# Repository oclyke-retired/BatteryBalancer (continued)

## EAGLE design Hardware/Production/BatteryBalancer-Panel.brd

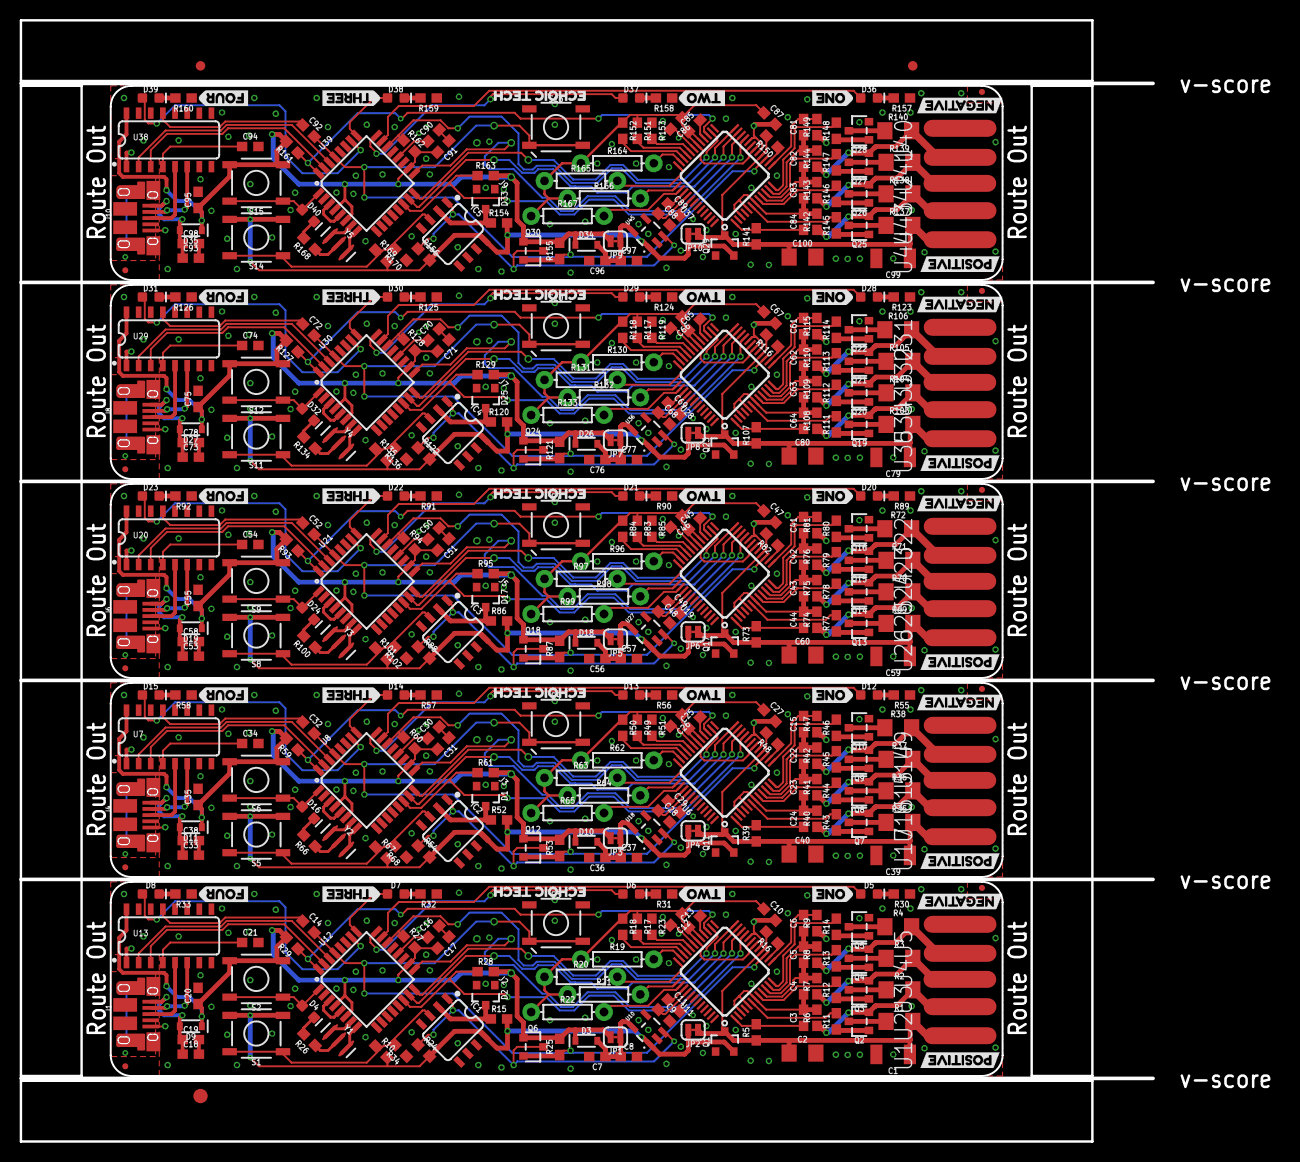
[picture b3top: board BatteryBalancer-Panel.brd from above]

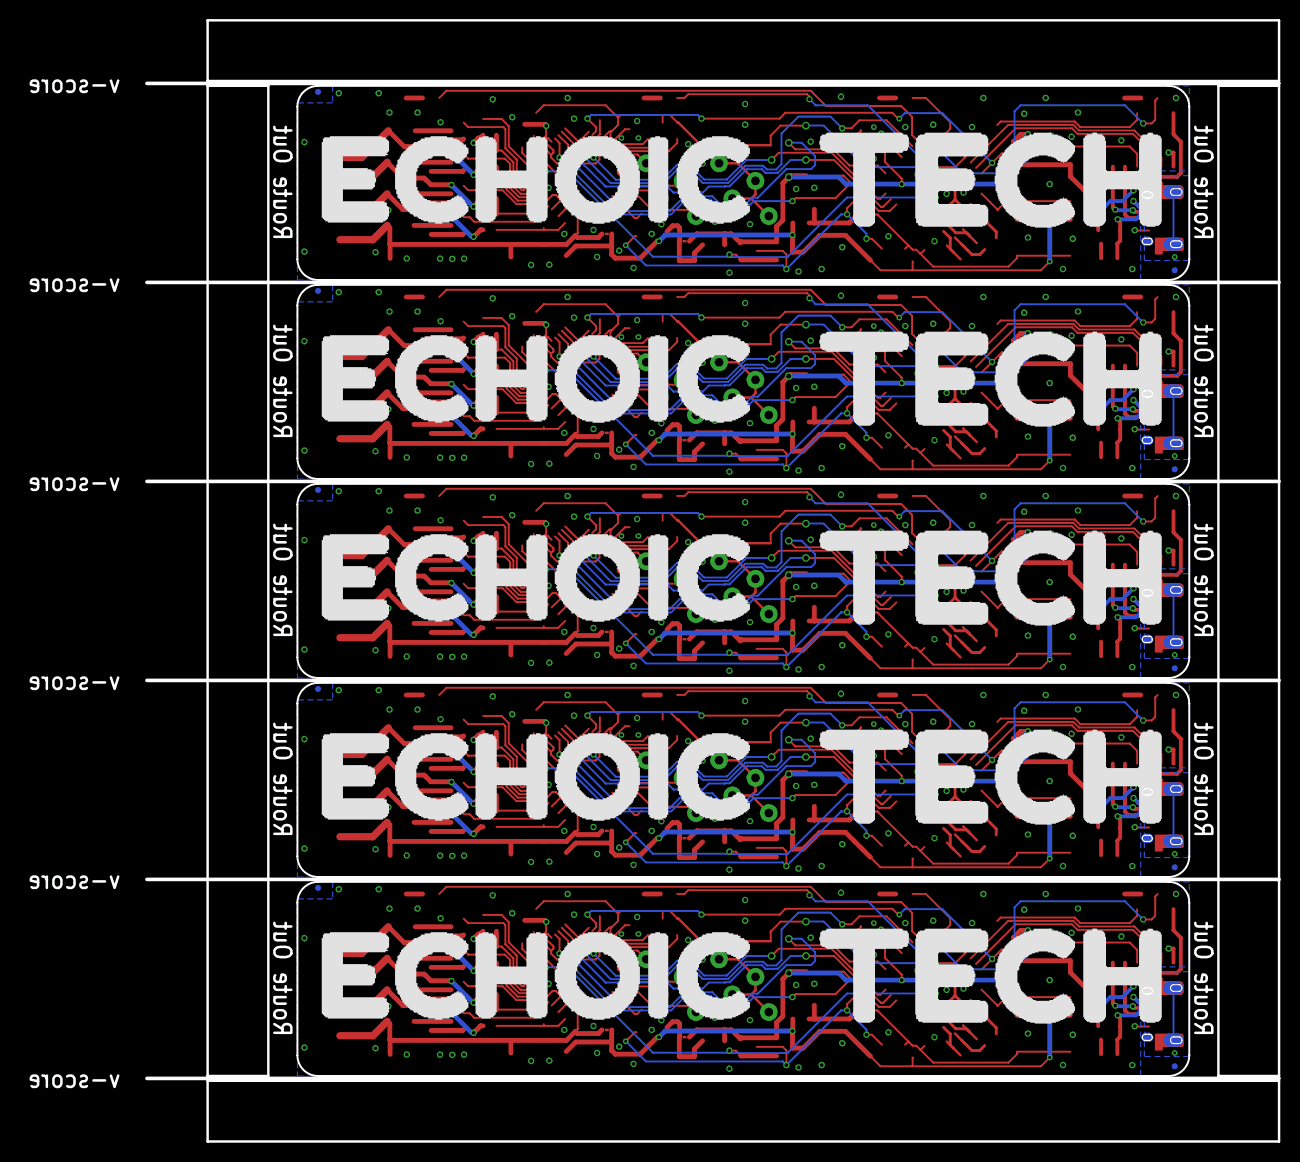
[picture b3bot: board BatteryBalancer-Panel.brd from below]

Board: 2 copper layers, 118.5 x 117.3 mm, 498 parts (20 on the bottom side), 335 nets.

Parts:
C1, C39, C59, C79, C99: 10uF; 1210
C2, C40, C60, C80, C100: 1.0uF; 1206
C3, C4, C5, C6, C8, C10, C12, C14, C15, C16, C17, C18, C20, C22, C23, C24, C26, C27, C30, C31, C32, C33, C35, C37, C41, C42, C43, C44, C46, C47, C50, C51, C52, C53, C55, C57, C61, C62, C63, C64, C66, C67, C70, C71, C72, C73, C75, C77, C81, C82, C83, C84, C86, C87, C90, C91, C92, C93, C95, C97: 0.1uF; 0603
C7, C9, C11, C13, C19, C25, C28, C29, C36, C38, C45, C48, C49, C56, C58, C65, C68, C69, C76, C78, C85, C88, C89, C96, C98: 1.0uF; 0603
C21, C34, C54, C74, C94: 10nF; 0603
D1, D2, D17, D25, D33: TH-12V; SOT23-3
D3, D9, D10, D11, D18, D19, D26, D27, D34, D35: 3A/10V/280mV; SOD-323
D4, D5, D6, D7, D8, D12, D13, D14, D15, D16, D20, D21, D22, D23, D24, D28, D29, D30, D31, D32, D36, D37, D38, D39, D40: BLUE; LED-0603
E$1, E$2: FIDUCIAL-1X2
E$3: FIDUCIAL-1.5X3
FD1, FD2, FD3, FD4, FD5, FD6, FD7, FD8, FD9, FD10, FD11, FD12, FD13, FD14, FD15, FD16, FD17, FD18, FD19, FD20: FIDUCIALUFIDUCIAL; FIDUCIAL-MICRO
IC1, IC2, IC3, IC4, IC5: OP-AMP; SO08
J1, J4, J6, J8, J10: USB-MICROB-PTH-MILL
J2, J3, J5, J7, J9: ISP; 2X3_TEST_POINTS
JP1, JP3, JP5, JP7, JP9: VCC; SMT-JUMPER_2_NC_TRACE_SILK
JP2, JP4, JP6, JP8, JP10: RPP_BYP; SMT-JUMPER_2_NC_TRACE_SILK
Q1, Q2, Q3, Q4, Q5, Q6, Q7, Q8, Q9, Q10, Q11, Q12, Q13, Q14, Q15, Q16, Q17, Q18, Q19, Q20, Q21, Q22, Q23, Q24, Q25, Q26, Q27, Q28, Q29, Q30: SOT23-3
R1, R2, R3, R4, R35, R36, R37, R38, R69, R70, R71, R72, R103, R104, R105, R106, R137, R138, R139, R140: 10; 1206
R5, R6, R7, R8, R9, R11, R12, R13, R14, R16, R17, R18, R23, R24, R25, R26, R27, R28, R29, R39, R40, R41, R42, R43, R44, R45, R46, R47, R48, R49, R50, R51, R53, R54, R59, R60, R61, R66, R73, R74, R75, R76, R77, R78, R79, R80, R81, R82, R83, R84, R85, R87, R88, R93, R94, R95, R100, R107, R108, R109, R110, R111, R112, R113, R114, R115, R116, R117, R118, R119, R121, R122, R127, R128, R129, R134, R141, R142, R143, R144, R145, R146, R147, R148, R149, R150, R151, R152, R153, R155, R156, R161, R162, R163, R168: 10k; 0603
R10, R15, R52, R67, R86, R101, R120, R135, R154, R169: 330k; 0603
R19, R20, R21, R22, R62, R63, R64, R65, R96, R97, R98, R99, R130, R131, R132, R133, R164, R165, R166, R167: DNP; AXIAL-0.3
R30, R31, R32, R33, R55, R56, R57, R58, R89, R90, R91, R92, R123, R124, R125, R126, R157, R158, R159, R160: 1k; 0603
R34, R68, R102, R136, R170: 10M; 0603
S1, S5, S8, S11, S14: Force Charge; TACTILE_SWITCH_SMD_5.2MM
S2, S6, S9, S12, S15: TEST; TACTILE_SWITCH_SMD_5.2MM
S3, S4, S7, S10, S13: Tall Switch; TACTILE_SWITCH_SMD_5.2MM
U1, U2, U3, U4, U5, U9, U14, U15, U16, U17, U22, U23, U24, U25, U26, U31, U32, U33, U34, U35, U40, U41, U42, U43, U44: TAP_POINT; 1X01_SMD_0.1IN
U6, U11, U19, U28, U37: AD7280A; LQFP-48
U7, U13, U20, U29, U38: CH340C; SO016
U8, U12, U21, U30, U39: ATMEGA328P_TQFP; TQFP32-08
U10, U18, U27, U36, U45: MCP1755; SOT23-5
U$1, U$11, U$20, U$29, U$38: POSITIVE1
U$2, U$10, U$19, U$28, U$37: NEGATIVE0
U$3, U$12, U$21, U$30, U$39: ONE3
U$4, U$13, U$22, U$31, U$40: TWO4
U$5, U$14, U$23, U$32, U$41: THREE6
U$6, U$15, U$24, U$33, U$42: FOUR5
U$7, U$16, U$25, U$34, U$43: ECHOIC_TECH7
U$8, U$17, U$26, U$35, U$44: ECHOIC#JPG
U$9, U$18, U$27, U$36, U$45: TECH#JPG
Y1, Y2, Y3, Y4, Y5: 16MHz; RESONATOR-SMD-3.2X1.3

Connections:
5V: C7.1, C8.1, D3.A, JP1.1, U10.5
5V1: C36.1, C37.1, D10.A, JP3.1, U18.5
5V2: C56.1, C57.1, D18.A, JP5.1, U27.5
5V3: C76.1, C77.1, D26.A, JP7.1, U36.5
5V4: C96.1, C97.1, D34.A, JP9.1, U45.5
!CS: R28.1, U11.21, U12.14
!CS1: R61.1, U6.21, U8.14
!CS2: R95.1, U19.21, U21.14
!CS3: R129.1, U28.21, U30.14
!CS4: R163.1, U37.21, U39.14
!CVNST: R27.1, U11.24, U12.22
!CVNST1: R60.1, U6.24, U8.22
!CVNST2: R94.1, U19.24, U21.22
!CVNST3: R128.1, U28.24, U30.22
!CVNST4: R162.1, U37.24, U39.22
!DTR: C14.1, U13.13
!DTR1: C32.1, U7.13
!DTR2: C52.1, U20.13
!DTR3: C72.1, U29.13
!DTR4: C92.1, U38.13
!RESET: C14.2, J2.5, Q6.2, R25.1, S3.3, S3.4, U11.15, U12.29
!RESET1: C32.2, J3.5, Q12.2, R53.1, S4.3, S4.4, U6.15, U8.29
!RESET2: C52.2, J5.5, Q18.2, R87.1, S7.3, S7.4, U19.15, U21.29
!RESET3: C72.2, J7.5, Q24.2, R121.1, S10.3, S10.4, U28.15, U30.29
!RESET4: C92.2, J9.5, Q30.2, R155.1, S13.3, S13.4, U37.15, U39.29
ALERT: R29.1, U11.27, U12.32
ALERT1: R59.1, U6.27, U8.32
ALERT2: R93.1, U19.27, U21.32
ALERT3: R127.1, U28.27, U30.32
ALERT4: R161.1, U37.27, U39.32
AREF: C16.1, U12.20
AREF1: C30.1, U8.20
AREF2: C50.1, U21.20
AREF3: C70.1, U30.20
AREF4: C90.1, U39.20
CHARGE: IC1.1, Q6.3, R24.1, U10.3
CHARGE1: IC2.1, Q12.3, R54.1, U18.3
CHARGE2: IC3.1, Q18.3, R88.1, U27.3
CHARGE3: IC4.1, Q24.3, R122.1, U36.3
CHARGE4: IC5.1, Q30.3, R156.1, U45.3
D+: J1.D+, U13.5
D+1: J4.D+, U7.5
D+2: J6.D+, U20.5
D+3: J8.D+, U29.5
D+4: J10.D+, U38.5
D-: J1.D-, U13.6
D-1: J4.D-, U7.6
D-2: J6.D-, U20.6
D-3: J8.D-, U29.6
D-4: J10.D-, U38.6
GND: C1.2, C2.2, C7.2, C8.2, C9.2, C10.2, C11.2, C12.2, C13.2, C16.2, C17.1, C18.2, C19.2, C20.2, C21.2, D2.1, IC1.4, J1.GND, J2.6, Q1.1, Q5.2, R9.1, R23.1, R26.1, R30.1, R31.1, R32.1, R33.1, R34.1, S3.1, S3.2, U5.1, U10.2, U11.17, U11.20, U11.28, U11.31, U11.41, U12.3, U12.5, U12.21, U13.1, Y1.2
GND1: C25.2, C26.2, C27.2, C28.2, C29.2, C30.2, C31.1, C33.2, C34.2, C35.2, C36.2, C37.2, C38.2, C39.2, C40.2, D1.1, IC2.4, J3.6, J4.GND, Q10.2, Q11.1, R47.1, R51.1, R55.1, R56.1, R57.1, R58.1, R66.1, R68.1, S4.1, S4.2, U6.17, U6.20, U6.28, U6.31, U6.41, U7.1, U8.3, U8.5, U8.21, U9.1, U18.2, Y2.2
GND2: C45.2, C46.2, C47.2, C48.2, C49.2, C50.2, C51.1, C53.2, C54.2, C55.2, C56.2, C57.2, C58.2, C59.2, C60.2, D17.1, IC3.4, J5.6, J6.GND, Q16.2, Q17.1, R81.1, R85.1, R89.1, R90.1, R91.1, R92.1, R100.1, R102.1, S7.1, S7.2, U19.17, U19.20, U19.28, U19.31, U19.41, U20.1, U21.3, U21.5, U21.21, U22.1, U27.2, Y3.2
GND3: C65.2, C66.2, C67.2, C68.2, C69.2, C70.2, C71.1, C73.2, C74.2, C75.2, C76.2, C77.2, C78.2, C79.2, C80.2, D25.1, IC4.4, J7.6, J8.GND, Q22.2, Q23.1, R115.1, R119.1, R123.1, R124.1, R125.1, R126.1, R134.1, R136.1, S10.1, S10.2, U28.17, U28.20, U28.28, U28.31, U28.41, U29.1, U30.3, U30.5, U30.21, U31.1, U36.2, Y4.2
GND4: C85.2, C86.2, C87.2, C88.2, C89.2, C90.2, C91.1, C93.2, C94.2, C95.2, C96.2, C97.2, C98.2, C99.2, C100.2, D33.1, IC5.4, J9.6, J10.GND, Q28.2, Q29.1, R149.1, R153.1, R157.1, R158.1, R159.1, R160.1, R168.1, R170.1, S13.1, S13.2, U37.17, U37.20, U37.28, U37.31, U37.41, U38.1, U39.3, U39.5, U39.21, U40.1, U45.2, Y5.2
LED1: D5.A, U12.23
LED2: D6.A, U12.24
LED3: D7.A, U12.25
LED4: D8.A, U12.26
LED5: D12.A, U8.23
LED6: D13.A, U8.24
LED7: D14.A, U8.25
LED8: D15.A, U8.26
LED9: D20.A, U21.23
LED10: D21.A, U21.24
LED11: D22.A, U21.25
LED12: D23.A, U21.26
LED13: D28.A, U30.23
LED14: D29.A, U30.24
LED15: D30.A, U30.25
LED16: D31.A, U30.26
LED17: D36.A, U39.23
LED18: D37.A, U39.24
LED19: D38.A, U39.25
LED20: D39.A, U39.26
MISO: J2.1, U11.26, U12.16
MISO1: J3.1, U6.26, U8.16
MISO2: J5.1, U19.26, U21.16
MISO3: J7.1, U28.26, U30.16
MISO4: J9.1, U37.26, U39.16
MOSI: J2.4, U11.23, U12.15
MOSI1: J3.4, U6.23, U8.15
MOSI2: J5.4, U19.23, U21.15
MOSI3: J7.4, U28.23, U30.15
MOSI4: J9.4, U37.23, U39.15
unnamed: Q7.3, R35.1
unnamed: Q7.2, R36.2, R40.1, U16.1
unnamed: U12.7, Y1.1
unnamed: U12.8, Y1.3
unnamed: Q2.3, R1.1
unnamed: Q2.2, R2.2, R6.1, U2.1
unnamed: Q3.3, R2.1
unnamed: Q3.2, R3.2, R7.1, U3.1
unnamed: Q4.3, R3.1
unnamed: Q4.2, R4.2, R8.1, U4.1
unnamed: Q5.3, R4.1
unnamed: Q2.1, R11.1
unnamed: Q3.1, R12.1
unnamed: R16.1, U11.14
unnamed: Q4.1, R13.1
unnamed: Q5.1, R14.1
unnamed: C6.2, R9.2, U11.13
unnamed: R14.2, U11.12
unnamed: C5.2, C6.1, R8.2, U11.11
unnamed: R13.2, U11.10
unnamed: C4.2, C5.1, R7.2, U11.9
unnamed: R12.2, U11.8
unnamed: R22.P$2, U11.38
unnamed: R11.2, U11.6
unnamed: C3.1, R5.2, U11.1
unnamed: C3.2, C4.1, R6.2, U11.3, U11.5, U11.7
unnamed: C9.1, U11.40
unnamed: R17.2, U11.33
unnamed: C11.1, U11.39
unnamed: R23.2, U11.32
unnamed: R18.2, U11.34
unnamed: R21.P$2, U11.37
unnamed: R20.P$2, U11.36
unnamed: R19.P$2, U11.35
unnamed: Q8.3, R36.1
unnamed: Q8.2, R37.2, R41.1, U15.1
unnamed: D4.C, R26.2
unnamed: C21.1, U13.4
unnamed: D8.C, R33.2
unnamed: IC1.3, R10.1, R34.2, S1.1, S1.2
unnamed: D2.3, IC1.2, R15.1
unnamed: D7.C, R32.2
unnamed: D6.C, R31.2
unnamed: D5.C, R30.2
unnamed: Q9.3, R37.1
unnamed: Q9.2, R38.2, R42.1, U14.1
unnamed: Q10.3, R38.1
unnamed: Q7.1, R43.1
unnamed: Q8.1, R44.1
unnamed: Q9.1, R45.1
unnamed: Q10.1, R46.1
unnamed: C15.2, R47.2, U6.13
unnamed: R46.2, U6.12
unnamed: C15.1, C22.2, R42.2, U6.11
unnamed: R45.2, U6.10
unnamed: C22.1, C23.2, R41.2, U6.9
unnamed: R44.2, U6.8
unnamed: R43.2, U6.6
unnamed: C24.1, R39.2, U6.1
unnamed: C23.1, C24.2, R40.2, U6.3, U6.5, U6.7
unnamed: R48.1, U6.14
unnamed: C28.1, U6.40
unnamed: C29.1, U6.39
unnamed: R51.2, U6.32
unnamed: R49.2, U6.33
unnamed: R50.2, U6.34
unnamed: U8.7, Y2.1
unnamed: U8.8, Y2.3
unnamed: C34.1, U7.4
unnamed: D1.3, IC2.2, R52.1
unnamed: IC2.3, R67.1, R68.2, S5.1, S5.2
unnamed: D15.C, R58.2
unnamed: D14.C, R57.2
unnamed: D13.C, R56.2
unnamed: D12.C, R55.2
unnamed: R65.P$2, U6.38
unnamed: R64.P$2, U6.37
unnamed: R63.P$2, U6.36
unnamed: R62.P$2, U6.35
unnamed: D16.C, R66.2
unnamed: Q13.3, R69.1
unnamed: Q13.2, R70.2, R74.1, U25.1
unnamed: Q14.3, R70.1
unnamed: Q14.2, R71.2, R75.1, U24.1
unnamed: Q15.3, R71.1
unnamed: Q15.2, R72.2, R76.1, U23.1
unnamed: Q16.3, R72.1
unnamed: Q13.1, R77.1
unnamed: Q14.1, R78.1
unnamed: Q15.1, R79.1
unnamed: Q16.1, R80.1
unnamed: C41.2, R81.2, U19.13
unnamed: R80.2, U19.12
unnamed: C41.1, C42.2, R76.2, U19.11
unnamed: R79.2, U19.10
unnamed: C42.1, C43.2, R75.2, U19.9
unnamed: R78.2, U19.8
unnamed: R77.2, U19.6
unnamed: C44.1, R73.2, U19.1
unnamed: C43.1, C44.2, R74.2, U19.3, U19.5, U19.7
unnamed: R82.1, U19.14
unnamed: C48.1, U19.40
unnamed: C49.1, U19.39
unnamed: R85.2, U19.32
unnamed: R83.2, U19.33
unnamed: R84.2, U19.34
unnamed: U21.7, Y3.1
unnamed: U21.8, Y3.3
unnamed: C54.1, U20.4
unnamed: D17.3, IC3.2, R86.1
unnamed: IC3.3, R101.1, R102.2, S8.1, S8.2
unnamed: D23.C, R92.2
unnamed: D22.C, R91.2
unnamed: D21.C, R90.2
unnamed: D20.C, R89.2
unnamed: R99.P$2, U19.38
unnamed: R98.P$2, U19.37
unnamed: R97.P$2, U19.36
unnamed: R96.P$2, U19.35
unnamed: D24.C, R100.2
unnamed: Q19.3, R103.1
unnamed: Q19.2, R104.2, R108.1, U34.1
unnamed: Q20.3, R104.1
unnamed: Q20.2, R105.2, R109.1, U33.1
unnamed: Q21.3, R105.1
unnamed: Q21.2, R106.2, R110.1, U32.1
unnamed: Q22.3, R106.1
unnamed: Q19.1, R111.1
unnamed: Q20.1, R112.1
unnamed: Q21.1, R113.1
unnamed: Q22.1, R114.1
unnamed: C61.2, R115.2, U28.13
unnamed: R114.2, U28.12
unnamed: C61.1, C62.2, R110.2, U28.11
unnamed: R113.2, U28.10
unnamed: C62.1, C63.2, R109.2, U28.9
unnamed: R112.2, U28.8
unnamed: R111.2, U28.6
unnamed: C64.1, R107.2, U28.1
unnamed: C63.1, C64.2, R108.2, U28.3, U28.5, U28.7
unnamed: R116.1, U28.14
unnamed: C68.1, U28.40
unnamed: C69.1, U28.39
unnamed: R119.2, U28.32
unnamed: R117.2, U28.33
unnamed: R118.2, U28.34
unnamed: U30.7, Y4.1
unnamed: U30.8, Y4.3
unnamed: C74.1, U29.4
unnamed: D25.3, IC4.2, R120.1
unnamed: IC4.3, R135.1, R136.2, S11.1, S11.2
unnamed: D31.C, R126.2
unnamed: D30.C, R125.2
unnamed: D29.C, R124.2
unnamed: D28.C, R123.2
unnamed: R133.P$2, U28.38
unnamed: R132.P$2, U28.37
unnamed: R131.P$2, U28.36
unnamed: R130.P$2, U28.35
unnamed: D32.C, R134.2
unnamed: Q25.3, R137.1
unnamed: Q25.2, R138.2, R142.1, U43.1
unnamed: Q26.3, R138.1
unnamed: Q26.2, R139.2, R143.1, U42.1
unnamed: Q27.3, R139.1
unnamed: Q27.2, R140.2, R144.1, U41.1
unnamed: Q28.3, R140.1
unnamed: Q25.1, R145.1
unnamed: Q26.1, R146.1
unnamed: Q27.1, R147.1
unnamed: Q28.1, R148.1
unnamed: C81.2, R149.2, U37.13
unnamed: R148.2, U37.12
unnamed: C81.1, C82.2, R144.2, U37.11
unnamed: R147.2, U37.10
unnamed: C82.1, C83.2, R143.2, U37.9
unnamed: R146.2, U37.8
unnamed: R145.2, U37.6
unnamed: C84.1, R141.2, U37.1
unnamed: C83.1, C84.2, R142.2, U37.3, U37.5, U37.7
unnamed: R150.1, U37.14
unnamed: C88.1, U37.40
unnamed: C89.1, U37.39
unnamed: R153.2, U37.32
unnamed: R151.2, U37.33
unnamed: R152.2, U37.34
unnamed: U39.7, Y5.1
unnamed: U39.8, Y5.3
unnamed: C94.1, U38.4
unnamed: D33.3, IC5.2, R154.1
unnamed: IC5.3, R169.1, R170.2, S14.1, S14.2
unnamed: D39.C, R160.2
unnamed: D38.C, R159.2
unnamed: D37.C, R158.2
unnamed: D36.C, R157.2
unnamed: R167.P$2, U37.38
unnamed: R166.P$2, U37.37
unnamed: R165.P$2, U37.36
unnamed: R164.P$2, U37.35
unnamed: D40.C, R168.2
RX-I: U12.30, U13.2
RX-I1: U7.2, U8.30
RX-I2: U20.2, U21.30
RX-I3: U29.2, U30.30
RX-I4: U38.2, U39.30
SCLK: J2.3, U11.22, U12.17
SCLK1: J3.3, U6.22, U8.17
SCLK2: J5.3, U19.22, U21.17
SCLK3: J7.3, U28.22, U30.17
SCLK4: J9.3, U37.22, U39.17
SHLD: J1.SHIELD, J1.SHIELD2, J1.SHIELD3, J1.SHIELD4, J1.SHIELD5, J1.SHIELD6, J1.SHIELD7, J1.SHIELD8, J1.SHIELD9, J1.SHIELD10
SHLD1: J4.SHIELD, J4.SHIELD2, J4.SHIELD3, J4.SHIELD4, J4.SHIELD5, J4.SHIELD6, J4.SHIELD7, J4.SHIELD8, J4.SHIELD9, J4.SHIELD10
SHLD2: J6.SHIELD, J6.SHIELD2, J6.SHIELD3, J6.SHIELD4, J6.SHIELD5, J6.SHIELD6, J6.SHIELD7, J6.SHIELD8, J6.SHIELD9, J6.SHIELD10
SHLD3: J8.SHIELD, J8.SHIELD2, J8.SHIELD3, J8.SHIELD4, J8.SHIELD5, J8.SHIELD6, J8.SHIELD7, J8.SHIELD8, J8.SHIELD9, J8.SHIELD10
SHLD4: J10.SHIELD, J10.SHIELD2, J10.SHIELD3, J10.SHIELD4, J10.SHIELD5, J10.SHIELD6, J10.SHIELD7, J10.SHIELD8, J10.SHIELD9, J10.SHIELD10
TEST: D4.A, S2.1, S2.2, U12.1
TEST1: D16.A, S6.1, S6.2, U8.1
TEST2: D24.A, S9.1, S9.2, U21.1
TEST3: D32.A, S12.1, S12.2, U30.1
TEST4: D40.A, S15.1, S15.2, U39.1
TX-O: U12.31, U13.3
TX-O1: U7.3, U8.31
TX-O2: U20.3, U21.31
TX-O3: U29.3, U30.31
TX-O4: U38.3, U39.31
USBVCC: C18.1, C19.1, D9.A, J1.VBUS
USBVCC1: C33.1, C38.1, D11.A, J4.VBUS
USBVCC2: C53.1, C58.1, D19.A, J6.VBUS
USBVCC3: C73.1, C78.1, D27.A, J8.VBUS
USBVCC4: C93.1, C98.1, D35.A, J10.VBUS
VCC: C17.2, C20.1, D3.C, D9.C, J2.2, JP1.2, Q6.1, R25.2, R27.2, R28.2, R29.2, S2.3, S2.4, U12.4, U12.6, U12.18, U13.16
VCC1: C31.2, C35.1, D10.C, D11.C, J3.2, JP3.2, Q12.1, R53.2, R59.2, R60.2, R61.2, S6.3, S6.4, U7.16, U8.4, U8.6, U8.18
VCC2: C51.2, C55.1, D18.C, D19.C, J5.2, JP5.2, Q18.1, R87.2, R93.2, R94.2, R95.2, S9.3, S9.4, U20.16, U21.4, U21.6, U21.18
VCC3: C71.2, C75.1, D26.C, D27.C, J7.2, JP7.2, Q24.1, R121.2, R127.2, R128.2, R129.2, S12.3, S12.4, U29.16, U30.4, U30.6, U30.18
VCC4: C91.2, C95.1, D34.C, D35.C, J9.2, JP9.2, Q30.1, R155.2, R161.2, R162.2, R163.2, S15.3, S15.4, U38.16, U39.4, U39.6, U39.18
VREG: C10.1, C12.1, C13.1, R17.1, R18.1, R19.P$1, R20.P$1, R21.P$1, R22.P$1, U11.18, U11.19, U11.29, U11.30
VREG1: C25.1, C26.1, C27.1, R49.1, R50.1, R62.P$1, R63.P$1, R64.P$1, R65.P$1, U6.18, U6.19, U6.29, U6.30
VREG2: C45.1, C46.1, C47.1, R83.1, R84.1, R96.P$1, R97.P$1, R98.P$1, R99.P$1, U19.18, U19.19, U19.29, U19.30
VREG3: C65.1, C66.1, C67.1, R117.1, R118.1, R130.P$1, R131.P$1, R132.P$1, R133.P$1, U28.18, U28.19, U28.29, U28.30
VREG4: C85.1, C86.1, C87.1, R151.1, R152.1, R164.P$1, R165.P$1, R166.P$1, R167.P$1, U37.18, U37.19, U37.29, U37.30
V_BATT: IC1.8, JP2.2, Q1.2, R10.2, R15.2, R24.2, S1.3, S1.4, U10.1
V_BATT1: IC2.8, JP4.2, Q11.2, R52.2, R54.2, R67.2, S5.3, S5.4, U18.1
V_BATT2: IC3.8, JP6.2, Q17.2, R86.2, R88.2, R101.2, S8.3, S8.4, U27.1
V_BATT3: IC4.8, JP8.2, Q23.2, R120.2, R122.2, R135.2, S11.3, S11.4, U36.1
V_BATT4: IC5.8, JP10.2, Q29.2, R154.2, R156.2, R169.2, S14.3, S14.4, U45.1
V_RAW: C1.1, C2.1, JP2.1, Q1.3, R1.2, R5.1, R16.2, U1.1, U11.16
V_RAW1: C39.1, C40.1, JP4.1, Q11.3, R35.2, R39.1, R48.2, U6.16, U17.1
V_RAW2: C59.1, C60.1, JP6.1, Q17.3, R69.2, R73.1, R82.2, U19.16, U26.1
V_RAW3: C79.1, C80.1, JP8.1, Q23.3, R103.2, R107.1, R116.2, U28.16, U35.1
V_RAW4: C99.1, C100.1, JP10.1, Q29.3, R137.2, R141.1, R150.2, U37.16, U44.1

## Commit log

2019-04-08 Going home
2019-04-11 Schematic mostly done, starting layout
2019-04-11 Routed 90%
    Needs finishing routing and also pretty graphics
2019-04-11 Did a DRC check
2019-04-12 Add spacious test board design
2019-04-12 Gerbered the testing board
2019-05-01 Panelized and ordered test board
2019-05-02 Implement LV shutoff circuit changes in schematic
    Switch to voltage-divider/zener comparator, change regulator enable to raw compararator output
2019-05-06 Began attempts to talk to the AD part
2019-05-07 SW: add crc calculation and initialization
    Proved communication with the device and implemented the suggested CRC algorithm
2019-05-07 Panelized + cammed
2019-05-16 Increase manufacturability, re panelize + CAM
